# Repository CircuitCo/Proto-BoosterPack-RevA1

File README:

The Proto BoosterPack allows you to plug your Stellaris LaunchPad into a double-wide proto board and provides access to all 40 signals on the expansion bus.  Two contacts per signal are available with standard proto boards. The Proto BoosterPack is designed to be compatible with the Stellaris Launchpad, but can also be used with MSP430 Launchpad. This board is designed by Sakoman Inc. For more information about the designer please visit http://www.sakoman.com/.

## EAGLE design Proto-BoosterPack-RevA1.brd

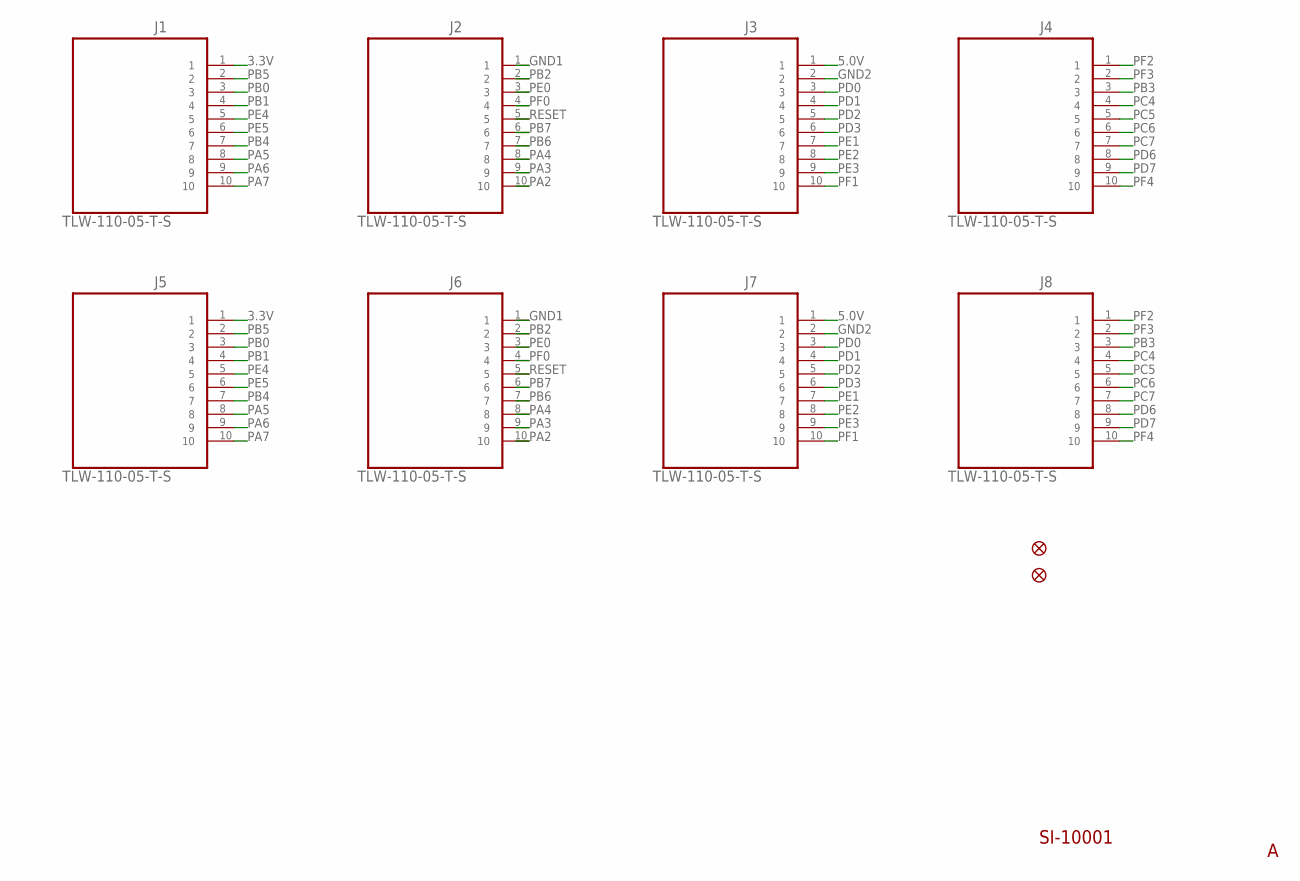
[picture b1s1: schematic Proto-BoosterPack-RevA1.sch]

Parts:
FID1, FID2: FIDUCIAL1X2; FIDUCIAL-1X2
J1, J5: TLW-110-05-T-S; SAMTEC_TLW-110-05-T-S
J2, J3, J4, J6, J7, J8: TLW-110-05-T-S; SAMTEC_TLW-110-05-T-S; MPN TLW-110-05-T-S

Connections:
3.3V: J1.1, J5.1
5.0V: J3.1, J7.1
GND1: J2.1, J6.1
GND2: J3.2, J7.2
PA2: J2.10, J6.10
PA3: J2.9, J6.9
PA4: J2.8, J6.8
PA5: J1.8, J5.8
PA6: J1.9, J5.9
PA7: J1.10, J5.10
PB0: J1.3, J5.3
PB1: J1.4, J5.4
PB2: J2.2, J6.2
PB3: J4.3, J8.3
PB4: J1.7, J5.7
PB5: J1.2, J5.2
PB6: J2.7, J6.7
PB7: J2.6, J6.6
PC4: J4.4, J8.4
PC5: J4.5, J8.5
PC6: J4.6, J8.6
PC7: J4.7, J8.7
PD0: J3.3, J7.3
PD1: J3.4, J7.4
PD2: J3.5, J7.5
PD3: J3.6, J7.6
PD6: J4.8, J8.8
PD7: J4.9, J8.9
PE0: J2.3, J6.3
PE1: J3.7, J7.7
PE2: J3.8, J7.8
PE3: J3.9, J7.9
PE4: J1.5, J5.5
PE5: J1.6, J5.6
PF0: J2.4, J6.4
PF1: J3.10, J7.10
PF2: J4.1, J8.1
PF3: J4.2, J8.2
PF4: J4.10, J8.10
RESET: J2.5, J6.5

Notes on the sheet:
SI-10001

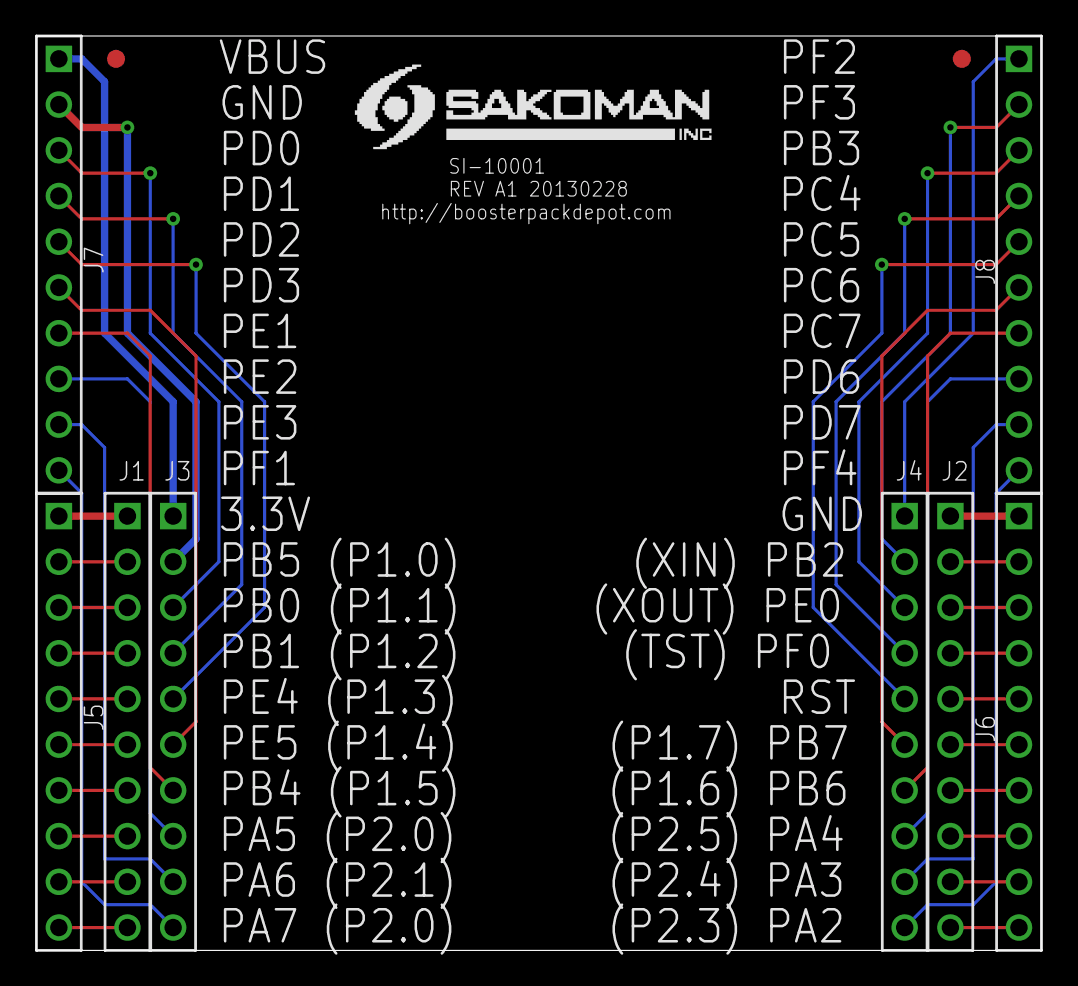
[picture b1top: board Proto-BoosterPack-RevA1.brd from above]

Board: 2 copper layers, 55.9 x 50.8 mm, 10 parts (0 on the bottom side), 40 nets.

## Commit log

2013-09-11 init-commit

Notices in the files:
parts and their libraries:
SparkFun-Aesthetics: Licensing: CC v3.0 Share-Alike You are welcome to use this library for commercial purposes.
